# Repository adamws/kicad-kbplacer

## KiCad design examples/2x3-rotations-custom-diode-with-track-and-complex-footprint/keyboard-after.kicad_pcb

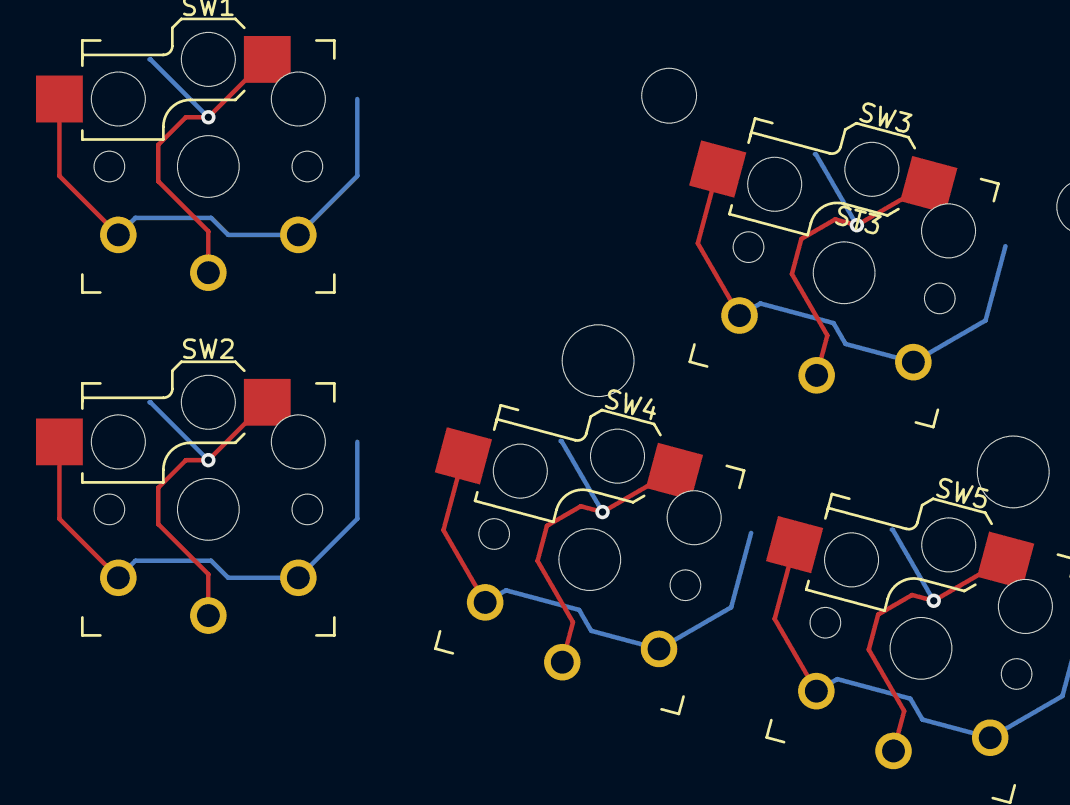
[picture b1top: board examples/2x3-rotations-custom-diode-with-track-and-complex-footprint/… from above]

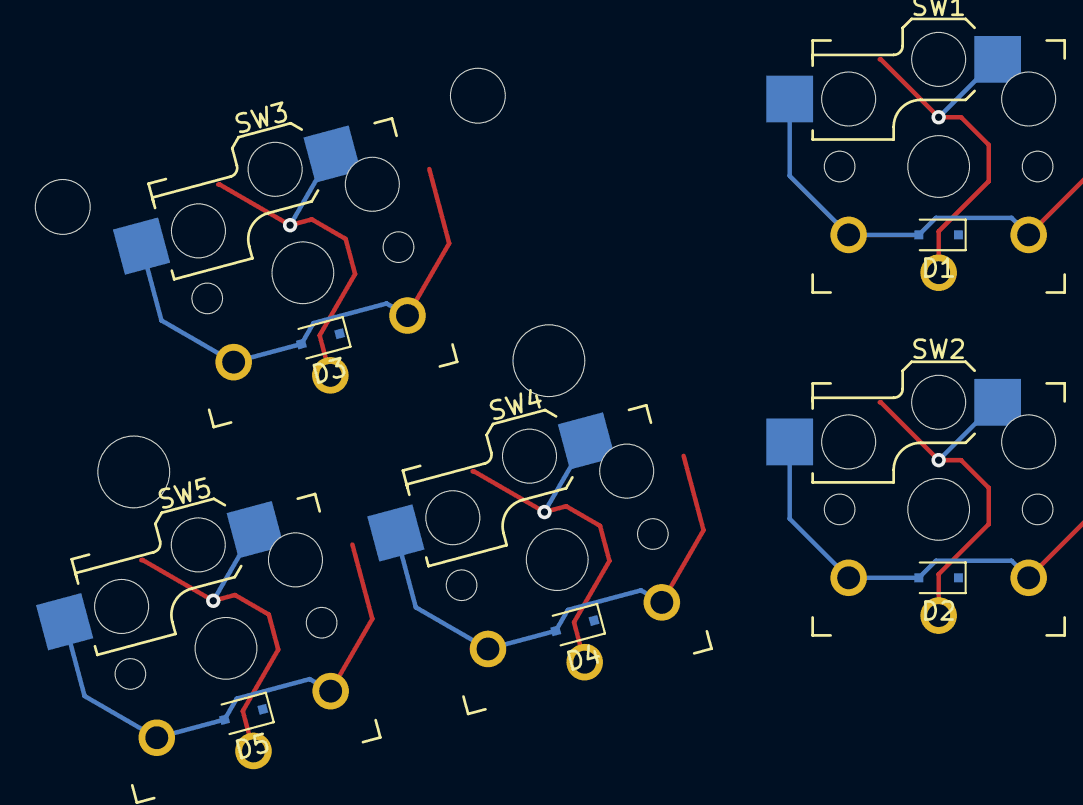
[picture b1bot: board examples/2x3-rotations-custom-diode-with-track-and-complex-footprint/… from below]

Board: 2 copper layers, 11 parts (5 on the bottom side), 9 nets.

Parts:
D1, D2, D3, D4, D5: D; D_SOD-323F
ST3: MountingHole; Stabilizer_Cherry_MX_2u
SW1, SW2, SW3, SW4, SW5: SW_Push; Kailh_socket_PG1350_optional_reversible

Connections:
COL0: SW1.1, SW2.1
COL1: SW3.1, SW4.1
unnamed: D1.2, SW1.2
unnamed: D2.2, SW2.2
unnamed: D3.2, SW3.2
unnamed: D4.2, SW4.2
unnamed: D5.2, SW5.2
ROW0: D1.1, D3.1
ROW1: D2.1, D4.1, D5.1

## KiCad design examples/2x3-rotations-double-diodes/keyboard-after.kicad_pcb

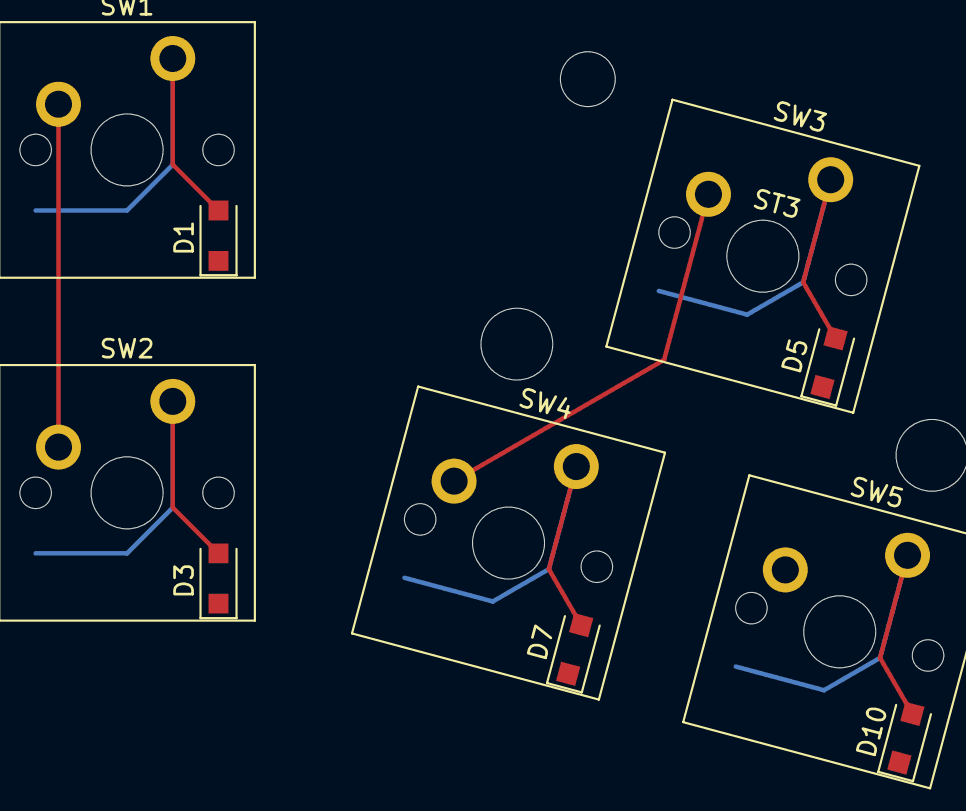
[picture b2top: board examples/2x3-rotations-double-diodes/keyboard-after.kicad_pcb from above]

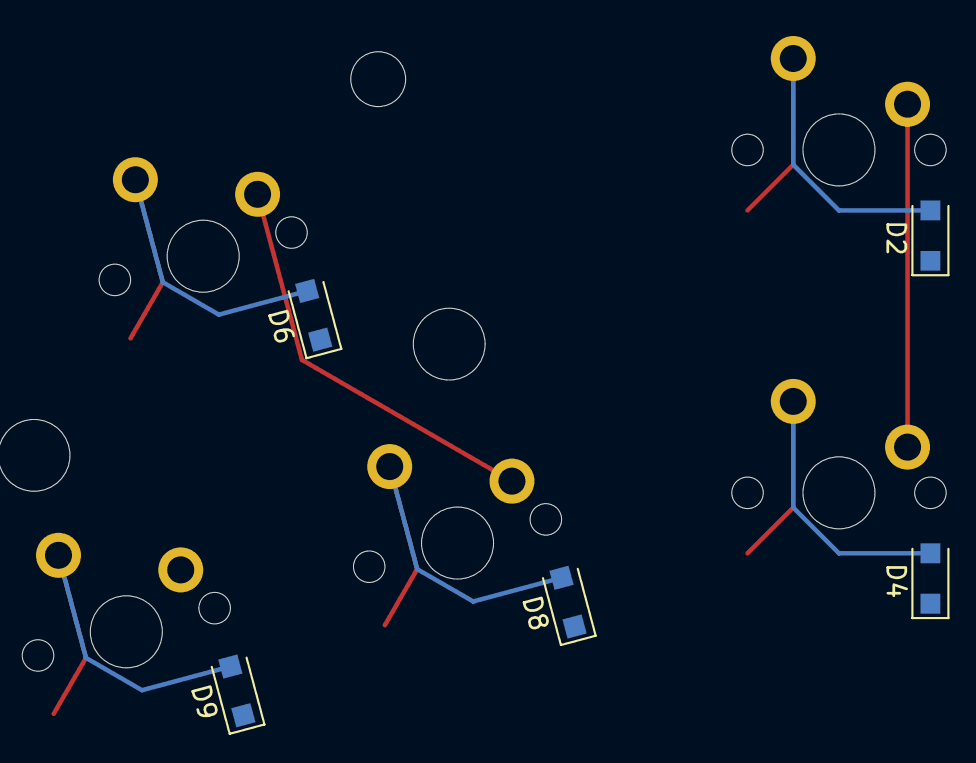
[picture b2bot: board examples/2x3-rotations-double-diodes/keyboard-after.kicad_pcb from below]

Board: 2 copper layers, 16 parts (5 on the bottom side), 9 nets.

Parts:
D1, D2, D3, D4, D5, D6, D7, D8, D9, D10: D; D_SOD-123F
ST3: MountingHole; Stabilizer_Cherry_MX_2u
SW1, SW2, SW4, SW5: SW_Push; SW_Cherry_MX_PCB_1.00u
SW3: SW_Push; SW_Cherry_MX_PCB_2.00u

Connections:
COL0: SW1.1, SW2.1
COL1: SW3.1, SW4.1
unnamed: D1.2, D2.2, SW1.2
unnamed: D3.2, D4.2, SW2.2
unnamed: D5.2, D6.2, SW3.2
unnamed: D7.2, D8.2, SW4.2
unnamed: D9.2, D10.2, SW5.2
ROW0: D1.1, D2.1, D5.1, D6.1
ROW1: D3.1, D4.1, D7.1, D8.1, D9.1, D10.1
